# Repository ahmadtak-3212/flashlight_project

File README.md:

# Flashlight: high-power LED driver

A handheld flashlight built around a **Cree XHP50.3 (6 V)** LED. The repo holds two threads of work:

1. **The power converter** (finished, documented in the final report): a discrete, analog, constant-current **boost converter** that takes 3 V from two alkaline cells up to about 6–6.5 V and regulates the LED at about 1–1.5 A. It uses op-amps, a comparator and a gate driver, with no microcontroller in the loop. It was built as the final project for MIT 6.2222 (fall 2025), including the graduate extension.
2. **The product boards** (in progress): an STM32 controller with shake-to-wake, a USB-PD charger and power-path board, and an integrated v1.1 board meant to put everything on a single 21700-cell PCB.

📄 **Read the final report:** [`docs/reports/final_report/final_report.pdf`](docs/reports/final_report/final_report.pdf) (the Typst source is next to it). The original proposal is in [`docs/reports/proposal/`](docs/reports/proposal).

---

## Contents

- [Status](#status)
- [Repository layout](#repository-layout)
- [How the converter works](#how-the-converter-works)
- [Boards](#boards)
- [Firmware](#firmware)
- [Analysis](#analysis)
- [Mechanical](#mechanical)
- [Reproducing the design](#reproducing-the-design)
- [Results](#results)
- [Known issues and next steps](#known-issues-and-next-steps)

## Status

| Area | Status |
|---|---|
| Boost LED driver (report design) | ✅ Built and measured on the bench (1 A LED current, stable closed loop) |
| Dev boards (`boost-dev`, `boost-dev-2`, `stm32-dev`, `led`) | ✅ Routed, with JLCPCB fab and assembly files |
| USB-PD power-input board | 🟡 Routed (4 layers, KiCad 8/9, May 2026); fab outputs need regenerating (see [known issues](#known-issues-and-next-steps)) |
| Integrated board `flashlight-full-v1-1` | 🟡 Schematic only (14 sheets), not laid out |
| Firmware (STM32 shake-to-wake) | 🟡 Proof of concept (~100 lines) |
| Mechanical (body, head, optic) | 🟡 SolidWorks assembly, not yet built |

## Repository layout

```
flashlight_project/
├── docs/
│   └── reports/
│       ├── final_report/     Typst source + PDF + figures (6.2222 final report)
│       └── proposal/         project proposal (Typst + PDF)
├── electrical/               one KiCad project per board (see "Boards")
├── firmware/
│   └── flashlight-firmware-stm32/   PlatformIO project (STM32L151, Arduino core)
├── analysis/
│   └── sim/boost_transfer.m  MATLAB state-space model of the boost + PI loop
└── mechanical/
    └── cad/flashlight-v1.SLDASM     SolidWorks assembly (body, head, optic, cell)
```

See [docs/STRUCTURE.md](docs/STRUCTURE.md) for the folder conventions shared across my projects.

## How the converter works

**Power stage.** A non-synchronous boost converter: a 22 µH inductor, a low-side switch, a Schottky rectifier and a 120 µF output capacitor. The LED returns to ground through a 0.2 Ω shunt.

| Parameter | Value |
|---|---|
| Input | 3 V (2 × alkaline cells) |
| Output | ≈ 6–6.5 V at the LED, 1–1.5 A (2 A hard ceiling) |
| Switching frequency | ≈ 100 kHz |
| Duty cycle | D ≈ 0.52 |
| Average inductor current | ≈ 3.9 A (ripple ≈ 0.7 A) |
| Inductor sizing | L_min ≈ 18 µH at 20 % ripple, so 22 µH chosen |
| Shunt dissipation | 0.45–0.8 W at 1.5–2 A |

**Control loop.** This is voltage-mode PWM with an outer LED-current loop, all built from analog parts:

1. An **LM358** amplifies the shunt voltage (current sense).
2. A second **LM358** stage acts as a PI controller and outputs V_ctrl. The model maps it with R_in = 10 kΩ and R_f = 680 Ω.
3. A third **LM358** generates a 0–1 V, ~100 kHz triangle.
4. An **LM311** comparator compares V_ctrl with the triangle to produce PWM.
5. An **IR2125** high-current gate driver drives the switch; a 12 V gate supply is needed for the GaN part.

**Switch comparison.** The same power stage was run with a silicon MOSFET (**RFD3055LESM**, ~107 mΩ) and a GaN FET (**GAN041-650WSBQ**, ~41 mΩ). Estimated device loss at the operating point is ≈ 84 mW for Si versus ≈ 18 mW for GaN, and the GaN part ran visibly cooler.

**Graduate extension.** The report adds a switched-capacitor quadrupler that charges a storage capacitor for a "flash" pulse through a 1 Ω series resistor (see “Graduate Extension” in the report).

The report also covers loop-shaping with Black's feedback formula and the boost converter's right-half-plane zero. It compares voltage-mode and current-mode control, drawing on the TI application notes it cites.

## Boards

All boards are KiCad projects under `electrical/`. Board renders are generated from the committed Gerbers.

| Board | What it is | Key parts | PCB |
|---|---|---|---|
| [`flashlight-boost-dev`](electrical/flashlight-boost-dev) | First IC-based LED boost test board | TPS61169 boost LED driver, NSR0240 Schottky, 4.7 µH WE-MAPI | 2 layers, 32 × 32 mm, JLCPCB files |
| [`flashlight-boost-dev-2`](electrical/flashlight-boost-dev-2) | Higher-power IC boost test board | TPS61500, 10 µH CDRH105R, SS36 3 A Schottky | 2 layers, 33 × 33 mm, JLCPCB files |
| [`flashlight-stm32-dev`](electrical/flashlight-stm32-dev) | "STM32L151C8 Battery Dev Board": controller and charging bring-up | STM32L151C8, BQ25185 charger/power path, MMA8452Q accelerometer, 2 × MCP1703A LDO, USB-C, ST-LINK header, 2 × 12 GPIO headers, RGB LED, 8 MHz + 32.768 kHz crystals | 6 layers, 120 × 35 mm, 99 parts, JLCPCB files |
| [`flashlight-led`](electrical/flashlight-led) | Small round LED carrier board | 3 LEDs, +18 V input | 2 layers, JLCPCB files |
| [`flashlight-power-input-dev`](electrical/flashlight-power-input-dev) | "100 W Power Delivery + Charger Module" | CYPD3177 USB-PD sink, BQ25792 buck-boost charger, BQ297xx protector, 4 × CSD16406Q3, 2 × LM5050-1 ideal diodes, TPS61222, TLV733, 21700 cell | 4 layers, 100 × 30 mm, 97 parts |
| [`flashlight-full-v1-1`](electrical/flashlight-full-v1-1) | Integrated flashlight (schematic) | STM32F070F6P, TPS61088 boost, BQ25185, BQ27220 fuel gauge, MMA8452Q, TMP102, INA180A1, MCP4017 digipot, IR2125, LM358 × 3, LM311, 74HC14, 2 × XHP50.3, 21700 cell, USB-C | 6-layer stackup, 14 schematic sheets, not laid out |
| `flashlight-hardware` | Empty placeholder project | — | — |

The early plan used TI boost-LED ICs (the two `boost-dev` boards). They could not deliver the current the XHP50.3 needs, which is why the report design went discrete.

<details>
<summary>Board renders (top and bottom)</summary>

**flashlight-boost-dev** (TPS61169)

**flashlight-boost-dev-2** (TPS61500)

**flashlight-stm32-dev**

</details>

## Firmware

`firmware/flashlight-firmware-stm32` is a PlatformIO project for the STM32L151 dev board. It shows the shake-to-toggle behavior:

- It configures the MMA8452Q **transient (shake) detector** over I²C on PB7/PB6: X/Y axes, threshold 12 (≈ 0.75 g), 25 × 20 ms debounce.
- The accelerometer interrupt on **PA0** wakes the MCU from deep sleep through `STM32LowPower`, and each shake toggles the output on **PB9**.

| Setting | Value |
|---|---|
| Platform | `ststm32`, Arduino framework |
| Board definition | `rak811_tracker` (an STM32L151 board used as a stand-in), with a local `boards/` directory |
| Libraries | `sparkfun/SparkFun_MMA8452Q ^1.4.0`, `stm32duino/STM32duino Low Power ^1.4.0` |
| Upload | `serial`: the STM32 ROM UART bootloader (hold BOOT0 high and reset) |

```bash
cd firmware/flashlight-firmware-stm32
pio run                     # build
pio run -t upload           # flash over the UART bootloader
# or use the board's ST-LINK header: set upload_protocol = stlink in platformio.ini
```

## Analysis

`analysis/sim/boost_transfer.m` (MATLAB) builds the averaged small-signal model of the boost, including the RHP zero. It wraps the PI controller around that model as an augmented state-space system, then plots the loop Bode response and the closed-loop setpoint step. Run it in MATLAB with the Control System Toolbox. The listing is also in the report appendix.

| Loop gain | Step response |
|---|---|
|  |  |

## Mechanical

`mechanical/cad/flashlight-v1.SLDASM` (SolidWorks) contains the body, head, a TIR 60° optic, an 18650 cell model, a copper slug for the LED, and the LED PCB. Mounting holders for the dev boards are in `electrical/<board>/holder/` (SLDPRT and STEP).

## Reproducing the design

| What | Tool |
|---|---|
| Schematics and PCBs | KiCad 8 or newer. `flashlight-power-input-dev` was last saved in KiCad 9. Projects use `${KIPRJMOD}`-relative libraries in each board's `libs/` folder. |
| PCB fab and assembly | Each board has `jlcpcb/gerber/` and `jlcpcb/production_files/` (Gerber zip, BOM and CPL) for JLCPCB. |
| Report | [Typst](https://typst.app) (`typst compile final_report.typ`) |
| Model | MATLAB with the Control System Toolbox |
| Firmware | PlatformIO (VS Code extension or `pio` CLI) |
| CAD | SolidWorks |

**Rebuilding the report converter on a bench.** Component values and schematic blocks are in the report's “Circuit Design and Analysis” chapter, which covers the power stage, current sense and PI loop, magnetics, and switch choice. “Hardware Implementation and Measurement Setup” covers the bench setup.

Bring-up order, from the report:
1. Run the boost open-loop at a fixed duty cycle into a resistive load.
2. Close the current loop at a low setpoint.
3. Raise the setpoint to the LED operating point.

The two fixes that mattered were:
- an RC filter (100 Ω / 1 nF) on the current-sense signal, and
- hysteresis on the LM311 comparator to stop chatter.

## Results

- The loop is closed and stable at about **1 A LED current** from a 3 V input. The output is 6–6.5 V, and the measured duty cycle is ≈ 0.5, close to the 0.52 predicted.
- The setpoint step response is well damped, as the MATLAB model predicts. Remaining differences come from LM358 bandwidth, comparator delay and the non-ideal ramp.
- GaN vs Si: both reach the same operating point, and the GaN FET runs cooler.
- The LED case settles near **70 °C** at the operating point. That is acceptable, but heatsinking through the copper slug is required.

| Bench setup | Thermal |
|---|---|
|  |  |

## Known issues and next steps

- The Gerbers in `electrical/flashlight-power-input-dev/jlcpcb/` are **copies of the mp3 player board**, left over from the project template. Regenerate them from `flashlight-power-input-dev.kicad_pcb` before ordering.
- `flashlight-full-v1-1` still needs layout. It merges the report's analog current loop (LM358/LM311/IR2125) with the STM32 controller, charger and fuel gauge.
- Firmware still needs brightness control through the digipot or PWM setpoint, battery reporting from the BQ27220, and thermal limiting from the TMP102.

## Author

Ahmad Taka.

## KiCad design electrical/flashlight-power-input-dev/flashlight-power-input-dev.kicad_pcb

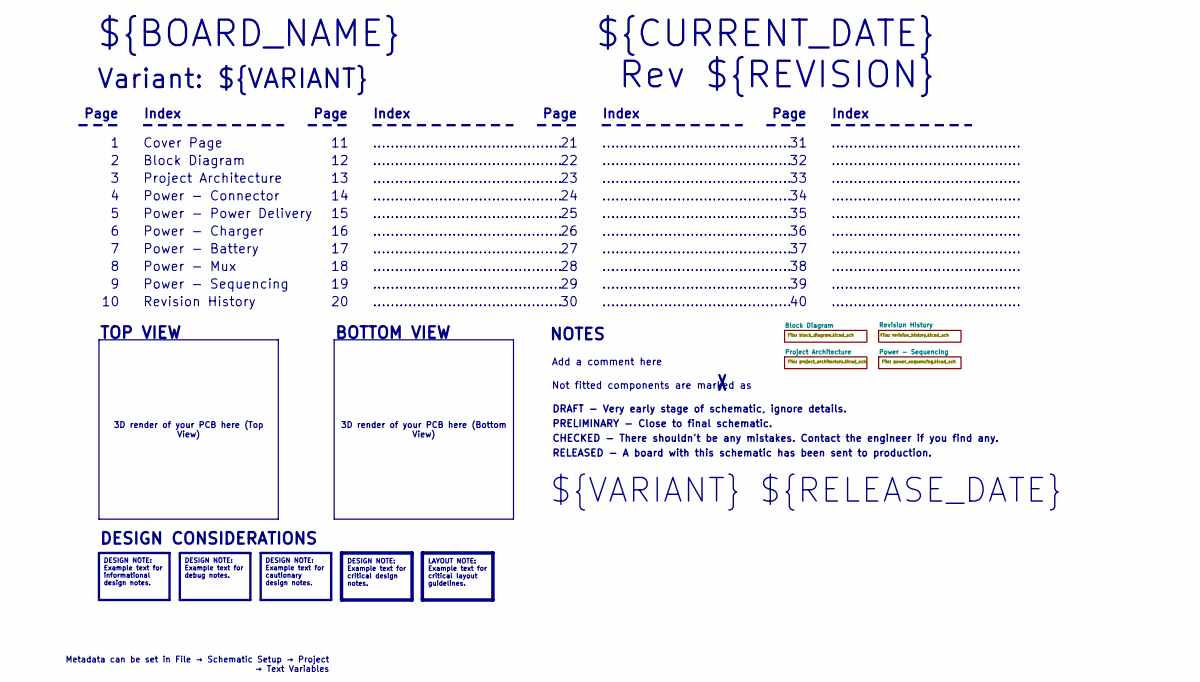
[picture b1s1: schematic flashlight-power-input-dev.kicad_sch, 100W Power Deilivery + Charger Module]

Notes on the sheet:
BOTTOM VIEW
...........................................
RELEASED - A board with this schematic has been sent to production.
Page
TOP VIEW
Revision History
Power - Sequencing
Power - Mux
Not fitted components are marked as
Index
PRELIMINARY - Close to final schematic.
${VARIANT} ${RELEASE_DATE}
Power - Connector
${CURRENT_DATE}
Variant: ${VARIANT}
Rev ${REVISION}
Power - Power Delivery
${BOARD_NAME}
DRAFT - Very early stage of schematic, ignore details.
Power - Charger
Block Diagram
Add a comment here
Cover Page
NOTES
Project Architecture
CHECKED - There shouldn't be any mistakes. Contact the engineer if you find any.
DESIGN CONSIDERATIONS
Power - Battery
3D render of your PCB here (Bottom View)
3D render of your PCB here (Top View)
Metadata can be set in File → Schematic Setup → Project → Text Variables
DESIGN NOTE: Example text for informational design notes.
LAYOUT NOTE: Example text for critical layout guidelines.
DESIGN NOTE: Example text for cautionary design notes.
DESIGN NOTE: Example text for debug notes.
DESIGN NOTE: Example text for critical design notes.

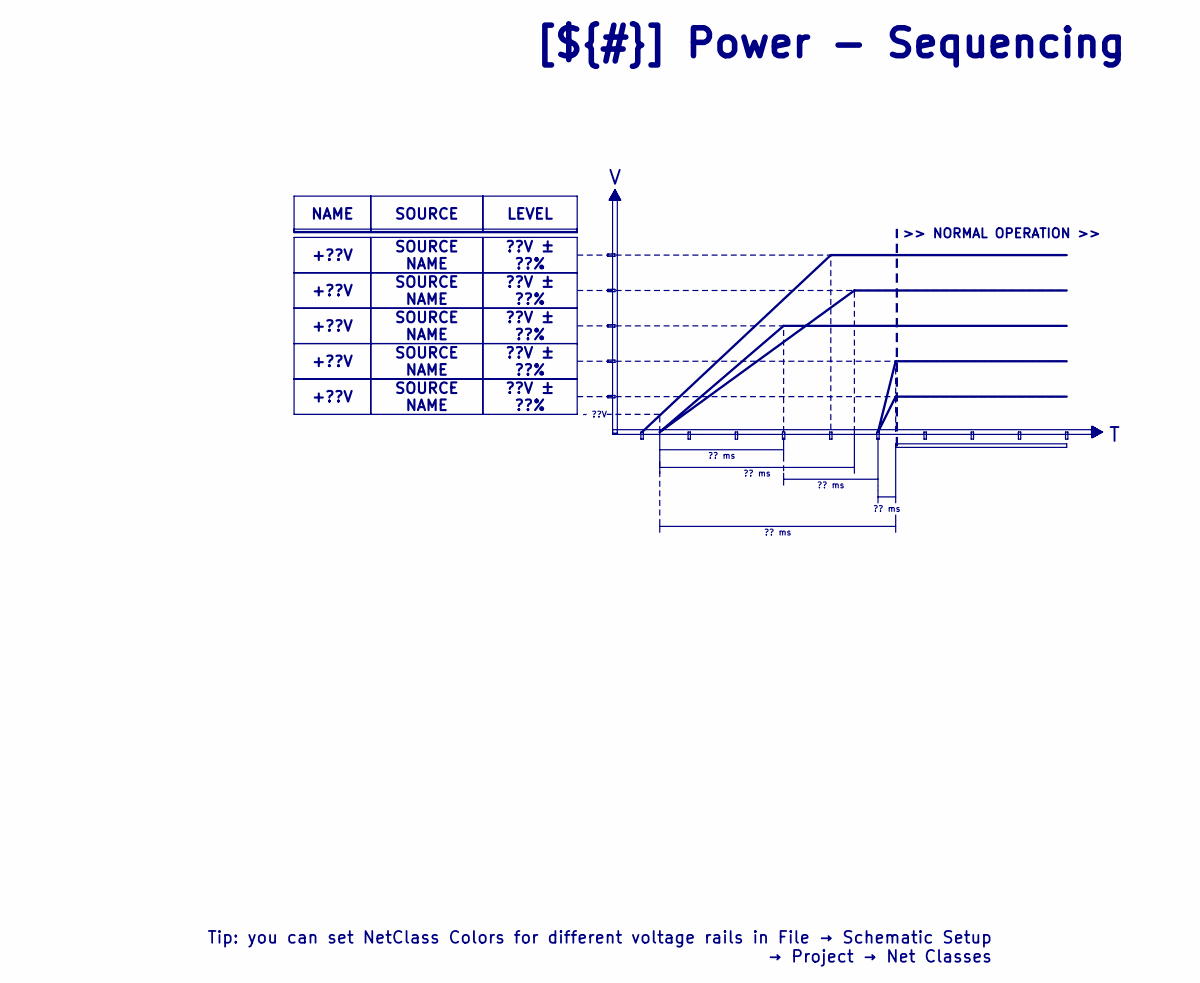
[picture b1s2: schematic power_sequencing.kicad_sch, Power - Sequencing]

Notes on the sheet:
>> NORMAL OPERATION >>
LEVEL
+??V
SOURCE NAME
?? ms
??V ± ??%
[${#}] ${TITLE}
~ ??V
NAME
SOURCE
Tip: you can set NetClass Colors for different voltage rails in File → Schematic Setup → Project → Net Classes

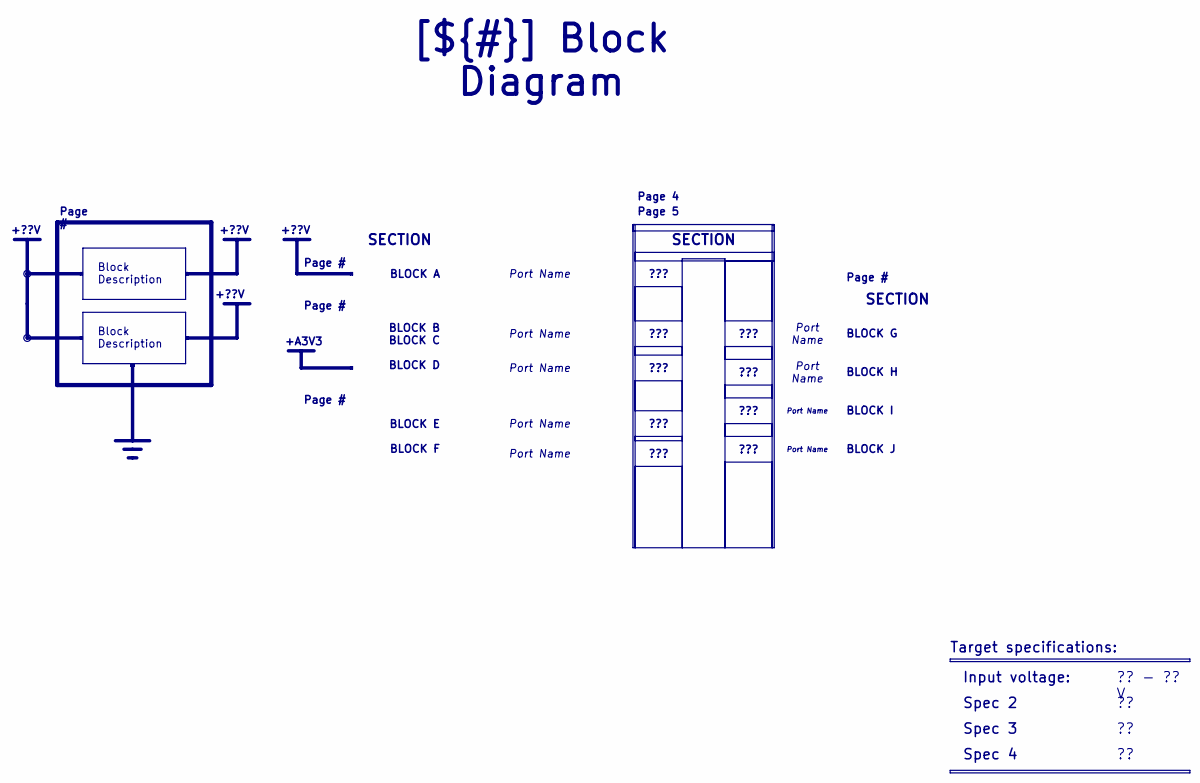
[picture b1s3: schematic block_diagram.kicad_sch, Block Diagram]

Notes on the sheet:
+??V
+A3V3
Spec 3
Block Description
???
Spec 2
Port Name
SECTION
Page #
Input voltage:
BLOCK E BLOCK F
BLOCK A
BLOCK I
BLOCK G
[${#}] ${TITLE}
Target specifications:
?? - ?? V
Page 4
BLOCK J
Page 5
BLOCK B BLOCK C BLOCK D
Spec 4
BLOCK H

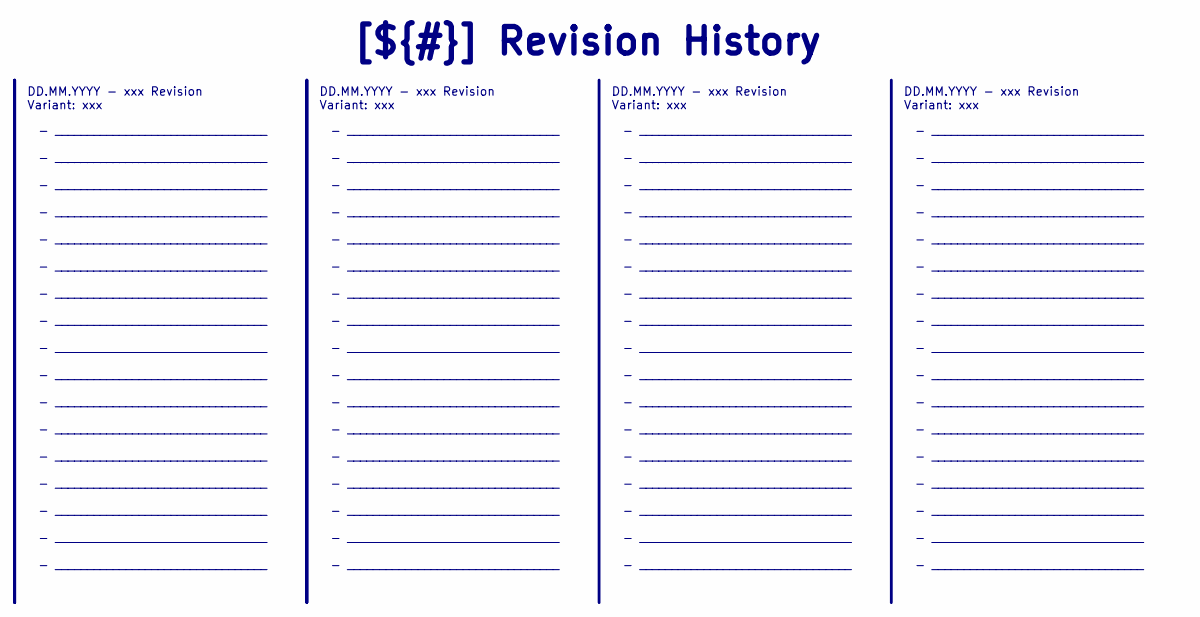
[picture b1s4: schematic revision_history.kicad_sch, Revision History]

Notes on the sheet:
- _________________________________ - _________________________________ - _________________________________ - _________________________________ - _________________________________ - _________________________________ - _________________________________ - _________________________________ - _________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
DD.MM.YYYY - xxx Revision Variant: xxx
[${#}] ${TITLE}

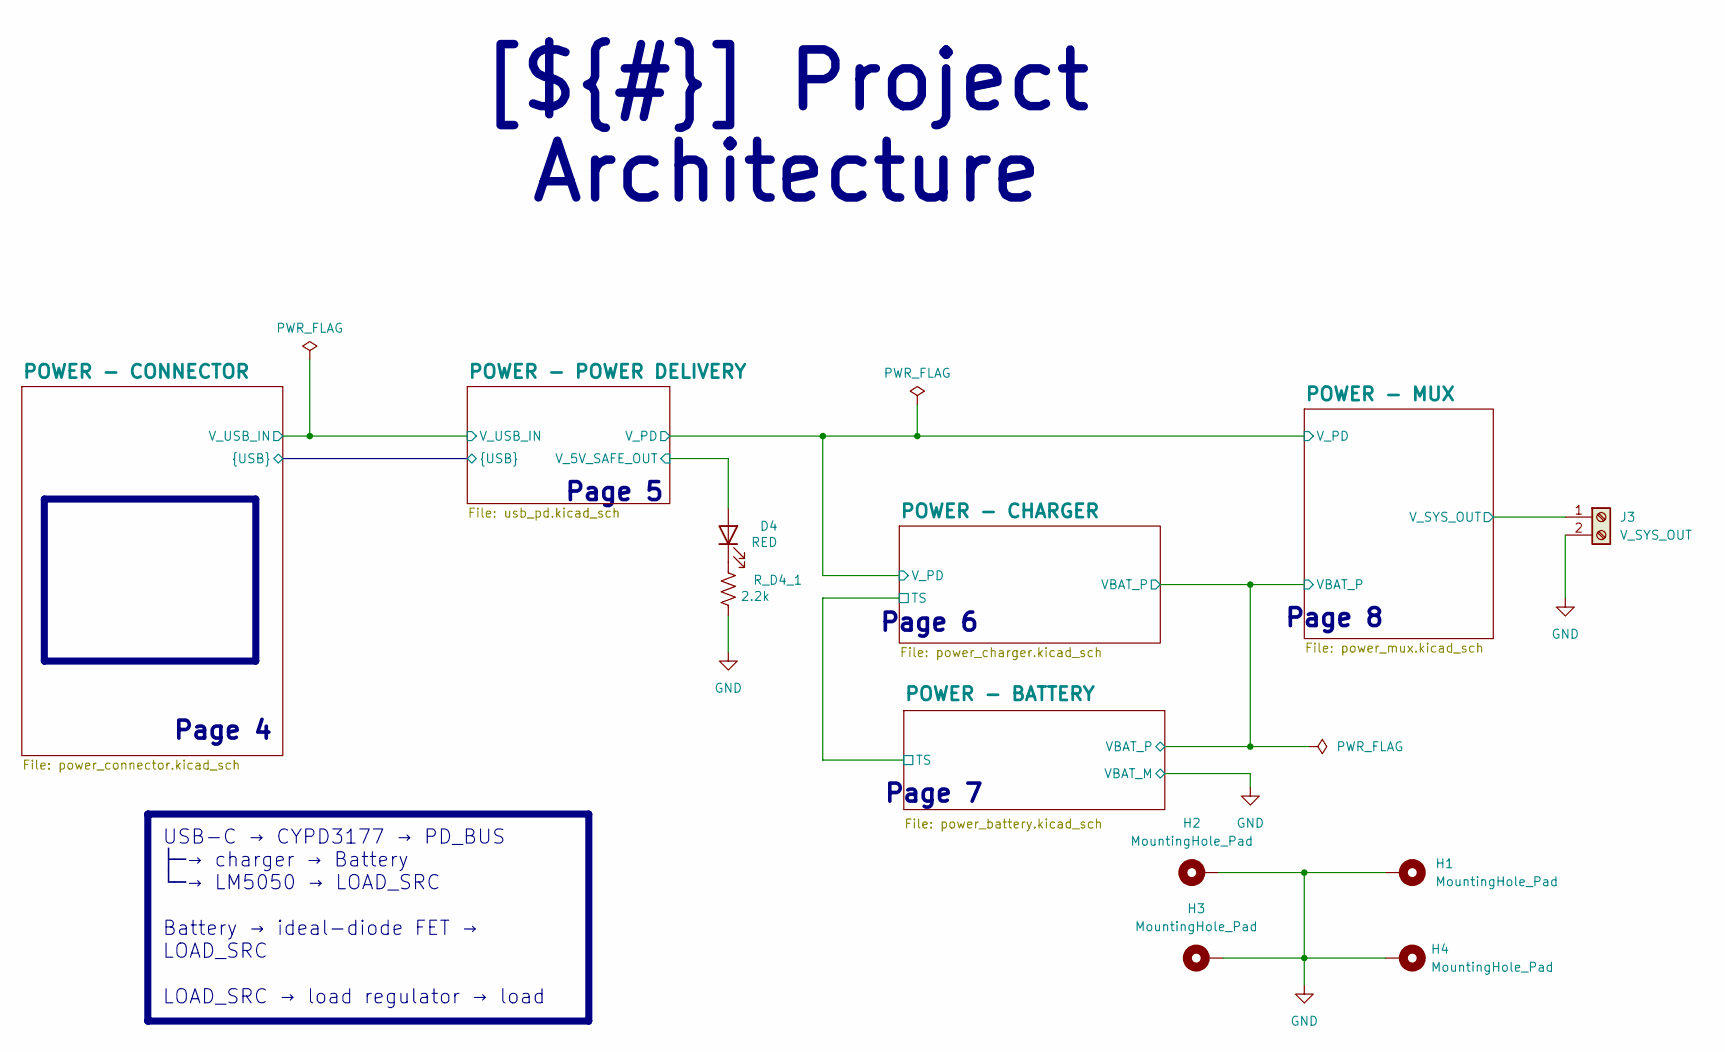
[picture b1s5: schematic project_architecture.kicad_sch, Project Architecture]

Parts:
D4: RED; LED_0603_1608Metric; LCSC C2286
H1, H2, H3, H4: MountingHole_Pad; MountingHole_3.2mm_M3_DIN965_Pad
J3: V_SYS_OUT; TerminalBlock_Phoenix_MKDS-1,5-2-5.08_1x02_P5.08mm_Horizont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
R_D4_1: 2.2k; R_0402_1005Metric; LCSC C25091

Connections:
/Project Architecture/POWER - MUX/V_SYS_OUT: J3.1; also elsewhere on the board
/Project Architecture/POWER - POWER DELIVERY/V_5V_SAFE_OUT: D4.2 (A); also elsewhere on the board
GND: H1.1 (1_1), H2.1 (1_1), H3.1 (1_1), H4.1 (1_1), J3.2, R_D4_1.1; also elsewhere on the board
unnamed: D4.1 (K), R_D4_1.2

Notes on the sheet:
Page 8
Page 5
Page 4
Page 6
Page 7
USB-C → CYPD3177 → PD_BUS ├─→ charger → Battery └─→ LM5050 → LOAD_SRC Battery → ideal-diode FET → LOAD_SRC LOAD_SRC → load regulator → load
[${#}] ${TITLE}

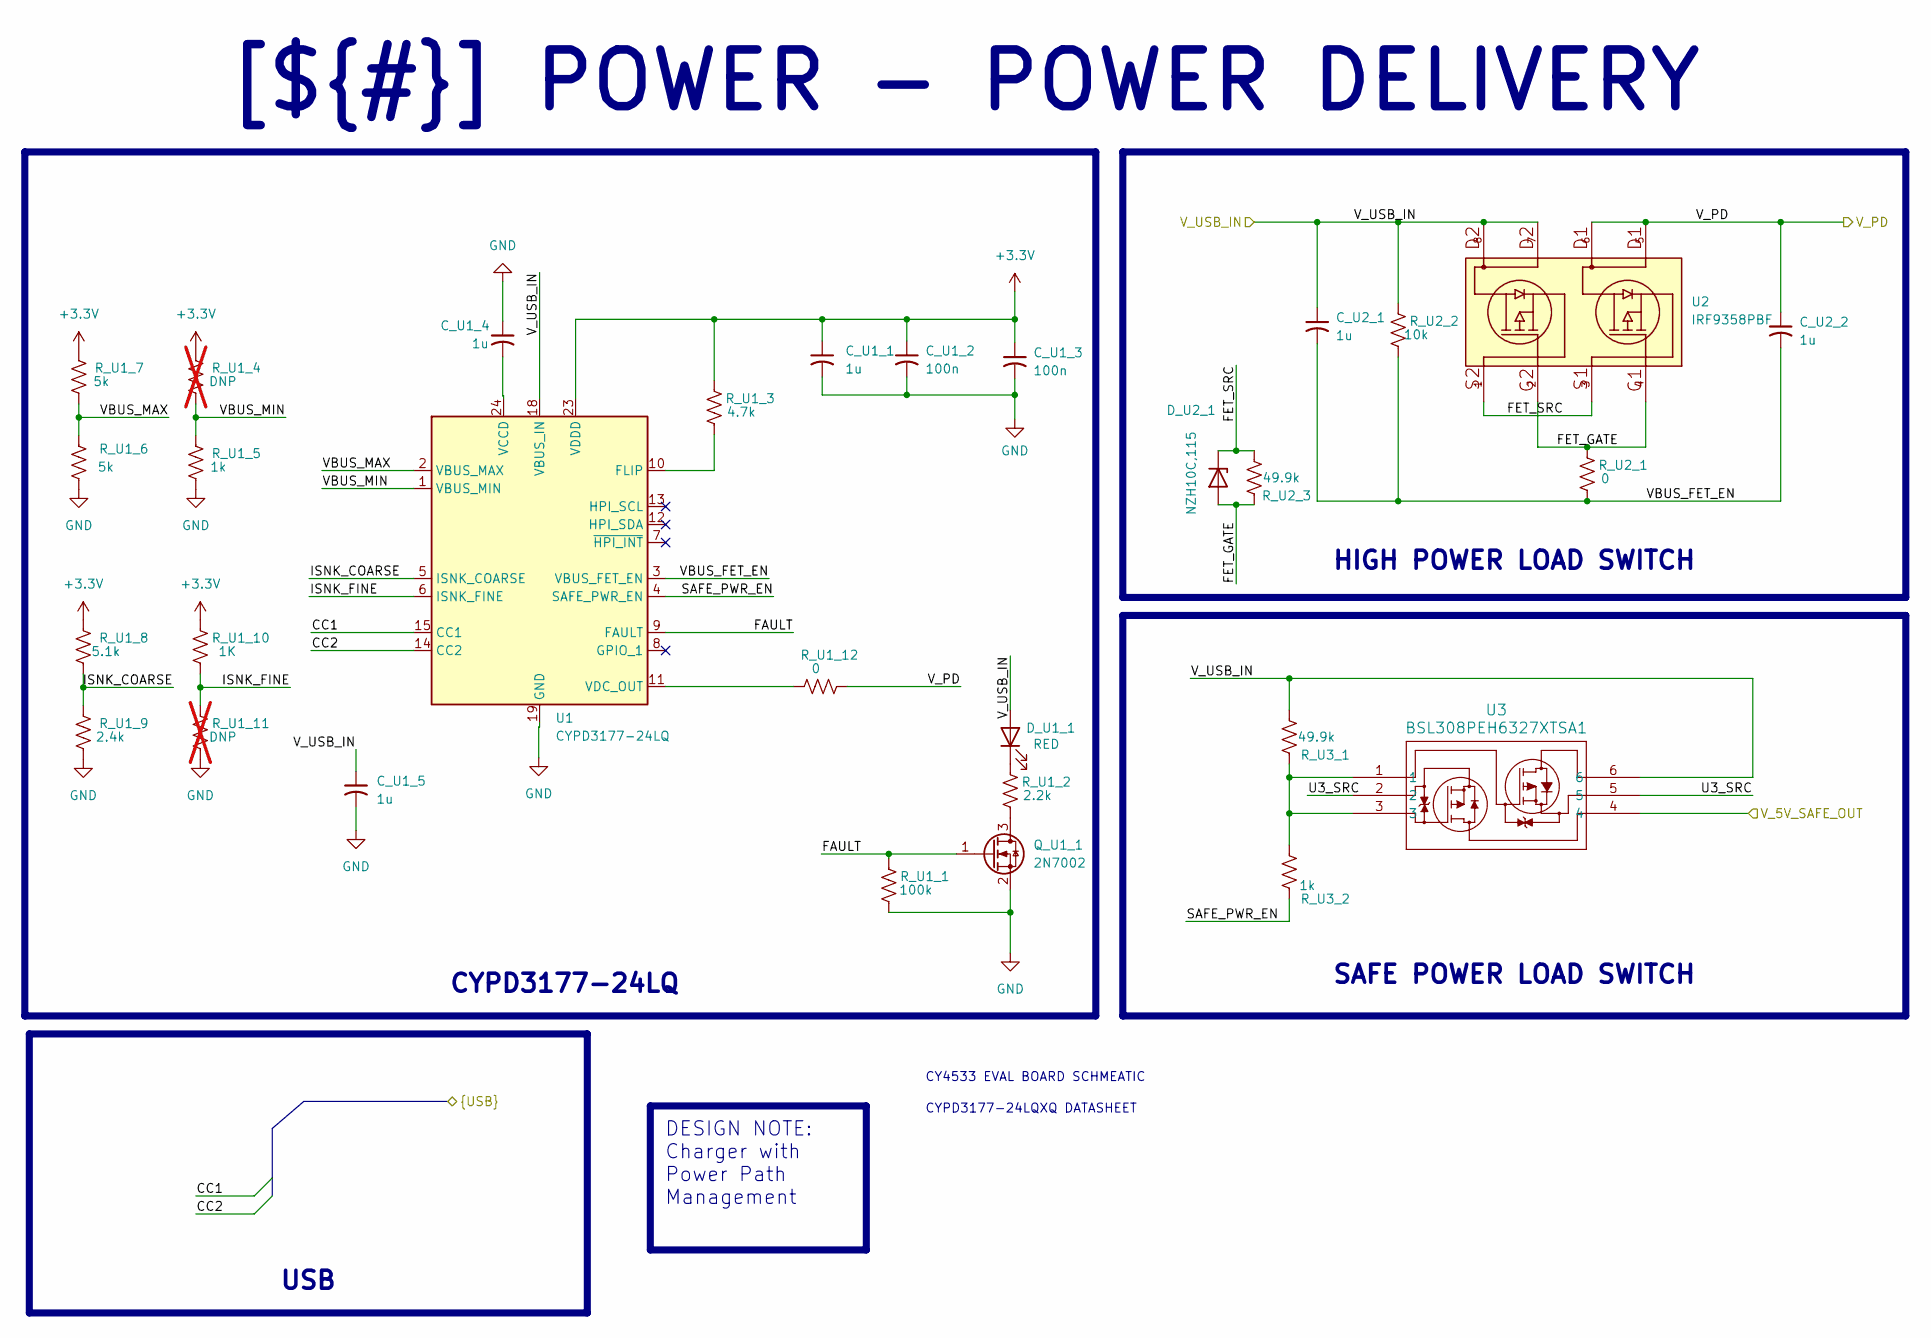
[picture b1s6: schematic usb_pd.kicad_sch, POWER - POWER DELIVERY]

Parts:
C_U1_1, C_U1_5, C_U2_1, C_U2_2: 1u; R_0603_1608Metric_Pad0.98x0.95mm_HandSolder
C_U1_2, C_U1_3: 100n; C_0402_1005Metric
C_U1_4: 1u; C_0402_1005Metric
D_U1_1: RED; LED_0603_1608Metric; LCSC C2286
D_U2_1: NZH10C,115; D_SOD-123F
Q_U1_1: 2N7002; SOT-23
R_U1_1: 100k; R_0402_1005Metric; LCSC C25091
R_U1_2: 2.2k; R_0402_1005Metric; LCSC C25091
R_U1_3: 4.7k; R_0402_1005Metric; LCSC C25091
R_U1_4, R_U1_11: DNP; R_0603_1608Metric_Pad0.98x0.95mm_HandSolder; LCSC C25091; not fitted
R_U1_5, R_U3_2: 1k; R_0603_1608Metric_Pad0.98x0.95mm_HandSolder; LCSC C25091
R_U1_6, R_U1_7: 5k; R_0603_1608Metric_Pad0.98x0.95mm_HandSolder; LCSC C25091
R_U1_8: 5.1k; R_0603_1608Metric_Pad0.98x0.95mm_HandSolder; LCSC C25091
R_U1_9: 2.4k; R_0603_1608Metric_Pad0.98x0.95mm_HandSolder; LCSC C25091
R_U1_10: 1K; R_0603_1608Metric_Pad0.98x0.95mm_HandSolder; LCSC C25091
R_U1_12, R_U2_1: 0; R_0603_1608Metric_Pad0.98x0.95mm_HandSolder; LCSC C25091
R_U2_2: 10k; R_0603_1608Metric_Pad0.98x0.95mm_HandSolder; LCSC C25091
R_U2_3, R_U3_1: 49.9k; R_0603_1608Metric_Pad0.98x0.95mm_HandSolder; LCSC C25091
U1: CYPD3177-24LQ; QFN-24-1EP_4x4mm_P0.5mm_EP2.75x2.75mm
U2: IRF9358PBF; SOIC8-150
U3: BSL308PEH6327XTSA1; PG-TSOP6-6-4_INF

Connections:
+3.3V: C_U1_1.1, C_U1_2.1, C_U1_3.1, R_U1_3.2, R_U1_4.2, R_U1_7.2, R_U1_8.2, R_U1_10.2, U1.23 (VDDD)
/Project Architecture/POWER - CHARGER/V_PD: C_U2_2.1, R_U1_12.1, U2.5, U2.6; also elsewhere on the board
/Project Architecture/POWER - CONNECTOR/CC1: U1.15 (CC1); also elsewhere on the board
/Project Architecture/POWER - CONNECTOR/CC2: U1.14 (CC2); also elsewhere on the board
/Project Architecture/POWER - POWER DELIVERY/FAULT: Q_U1_1.1 (G), R_U1_1.2, U1.9 (FAULT)
/Project Architecture/POWER - POWER DELIVERY/FET_GATE: D_U2_1.2 (A), R_U2_1.2, R_U2_3.1, U2.2, U2.4
/Project Architecture/POWER - POWER DELIVERY/FET_SRC: D_U2_1.1 (K), R_U2_3.2, U2.1, U2.3
/Project Architecture/POWER - POWER DELIVERY/ISNK_COARSE: R_U1_8.1, R_U1_9.2, U1.5 (ISNK_COARSE)
/Project Architecture/POWER - POWER DELIVERY/ISNK_FINE: R_U1_10.1, R_U1_11.2, U1.6 (ISNK_FINE)
/Project Architecture/POWER - POWER DELIVERY/SAFE_PWR_EN: R_U3_2.1, U1.4 (SAFE_PWR_EN)
/Project Architecture/POWER - POWER DELIVERY/U3_SRC: U3.2, U3.5
/Project Architecture/POWER - POWER DELIVERY/VBUS_FET_EN: C_U2_1.2, C_U2_2.2, R_U2_1.1, R_U2_2.1, U1.3 (VBUS_FET_EN)
/Project Architecture/POWER - POWER DELIVERY/VBUS_MAX: R_U1_6.2, R_U1_7.1, U1.2 (VBUS_MAX)
/Project Architecture/POWER - POWER DELIVERY/VBUS_MIN: R_U1_4.1, R_U1_5.2, U1.1 (VBUS_MIN)
/Project Architecture/POWER - POWER DELIVERY/V_5V_SAFE_OUT: U3.4; also elsewhere on the board
/Project Architecture/POWER - POWER DELIVERY/V_USB_IN: C_U1_5.1, C_U2_1.1, D_U1_1.2 (A), R_U2_2.2, R_U3_1.2, U1.18 (VBUS_IN), U2.7, U2.8, U3.6; also elsewhere on the board
GND: C_U1_1.2, C_U1_2.2, C_U1_3.2, C_U1_4.1, C_U1_5.2, Q_U1_1.2 (S), R_U1_1.1, R_U1_5.1, R_U1_6.1, R_U1_9.1, R_U1_11.1, U1.19 (GND), U1.22 (GND), U1.25 (GND); also elsewhere on the board
unnamed: D_U1_1.1 (K), R_U1_2.2
unnamed: Q_U1_1.3 (D), R_U1_2.1
unnamed: R_U3_1.1, R_U3_2.2, U3.1, U3.3
unnamed: R_U1_3.1, U1.10 (FLIP)
unnamed: C_U1_4.2, U1.24 (VCCD)
unnamed: R_U1_12.2, U1.11 (VDC_OUT)

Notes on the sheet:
CYPD3177-24LQXQ DATASHEET
CY4533 EVAL BOARD SCHMEATIC
[${#}] ${TITLE}
CYPD3177-24LQ
SAFE POWER LOAD SWITCH
DESIGN NOTE: Charger with Power Path Management
USB
HIGH POWER LOAD SWITCH

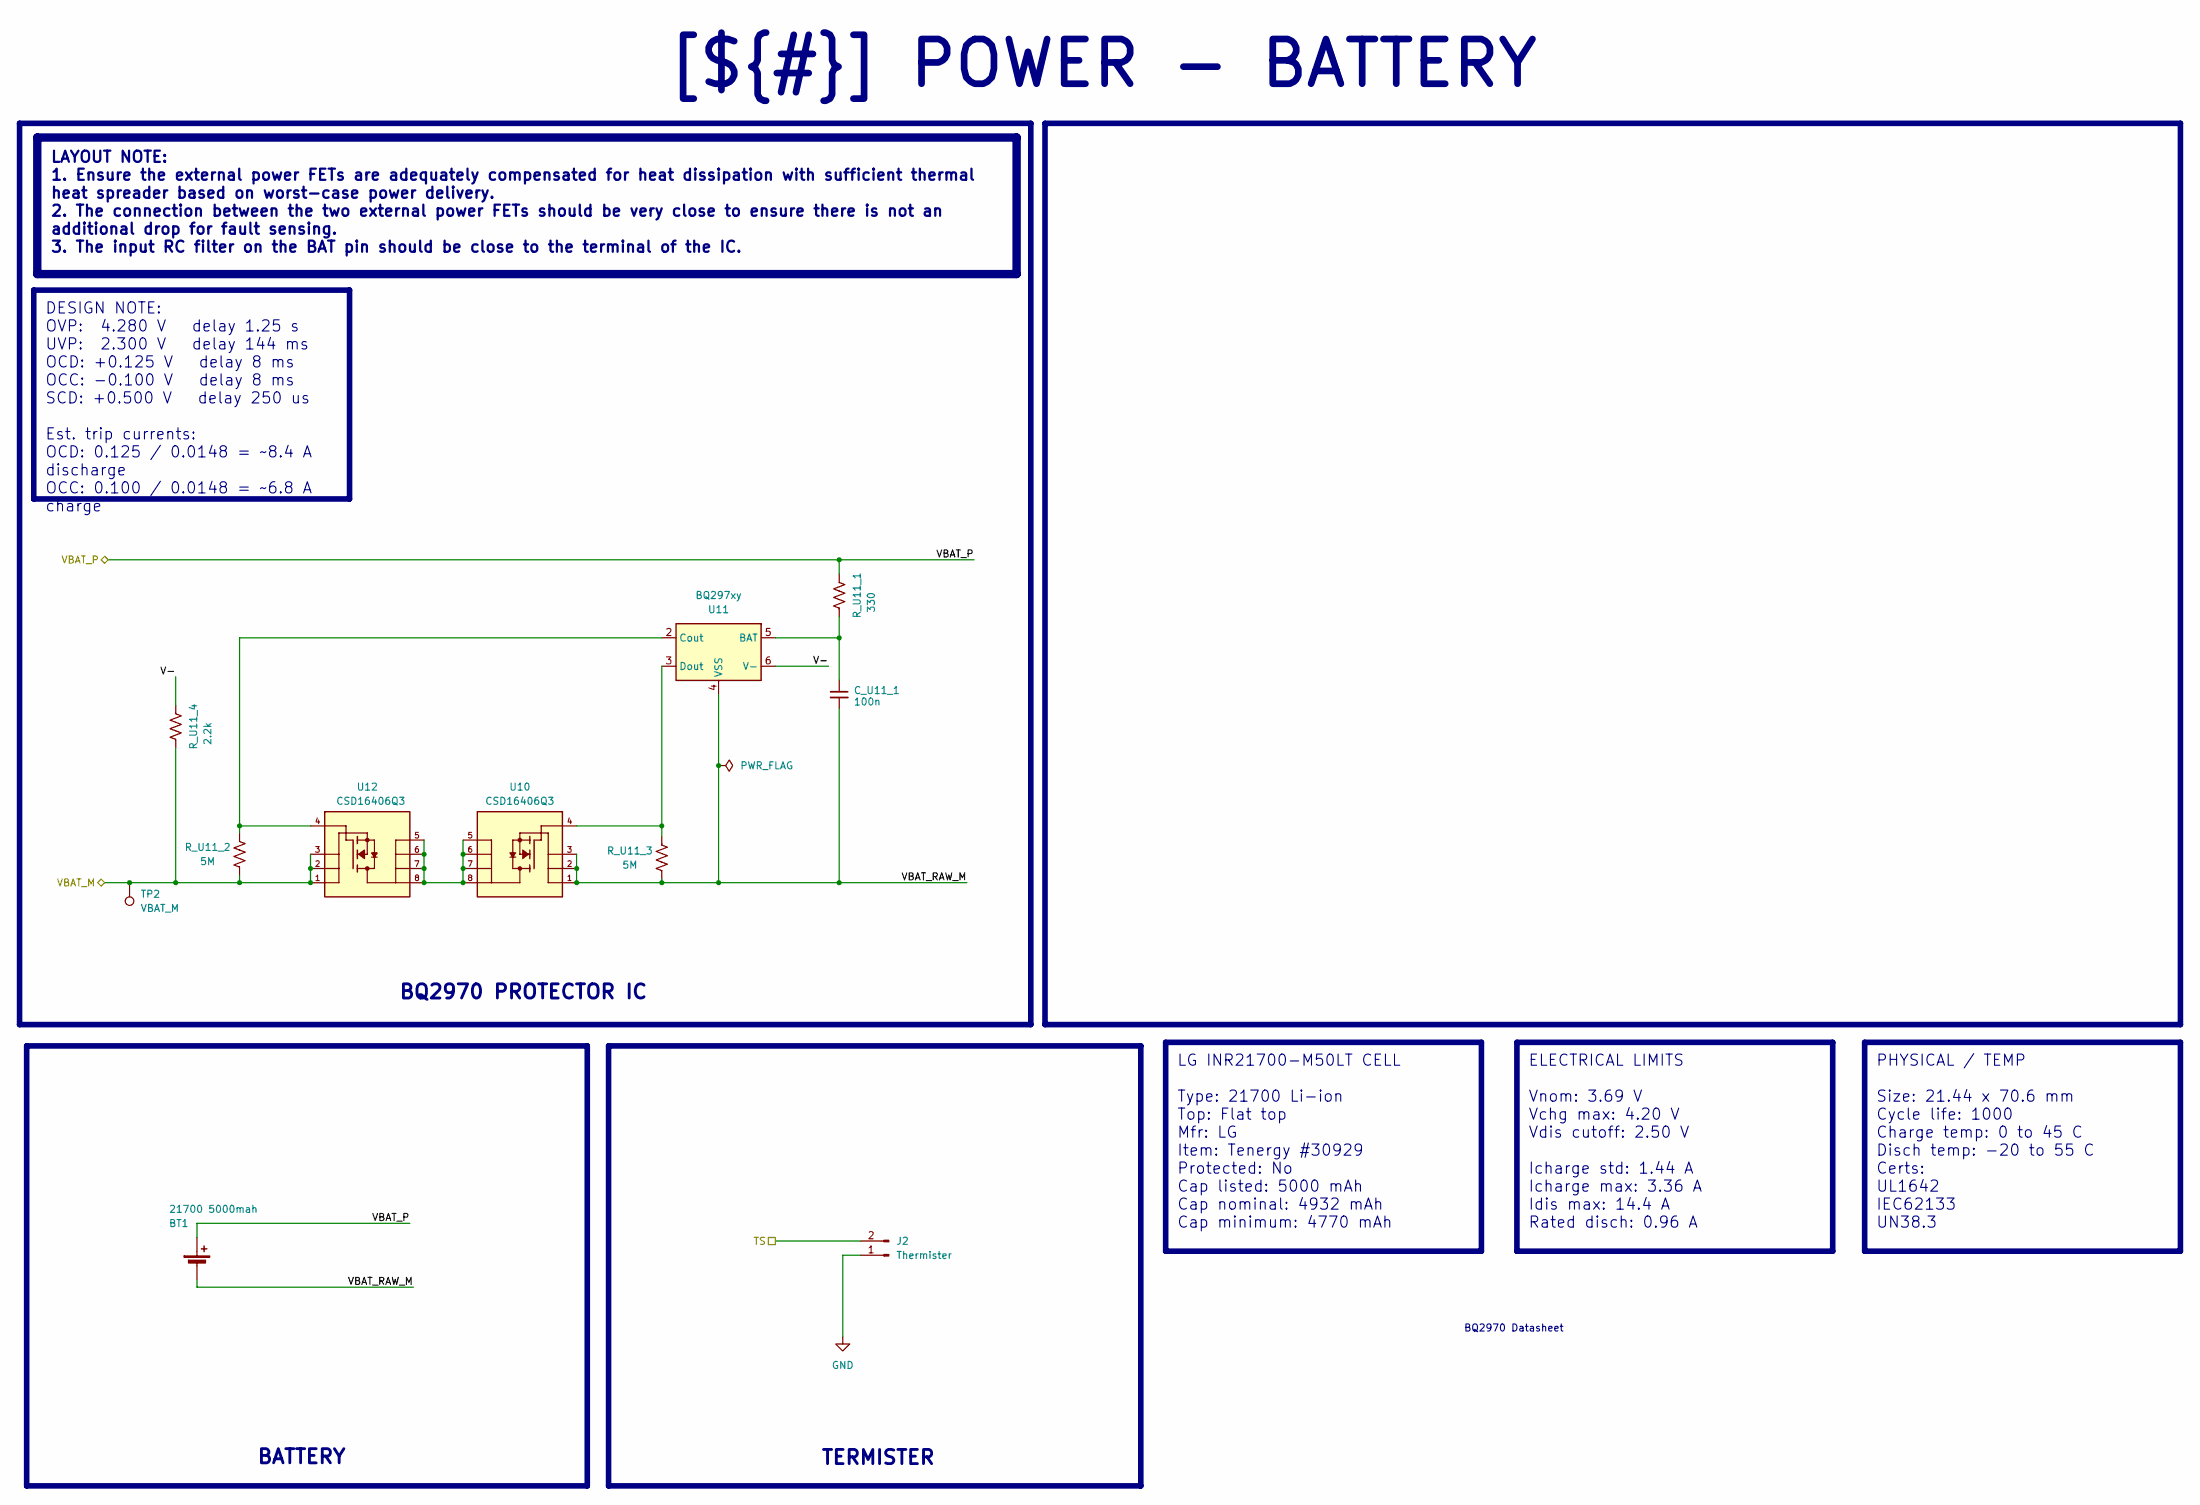
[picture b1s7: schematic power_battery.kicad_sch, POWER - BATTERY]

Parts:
BT1: 21700 5000mah; BISTOOK_BATTERY_HOLDER_21700
C_U11_1: 100n; C_0603_1608Metric; LCSC C1525
J2: Thermister; PinHeader_1x02_P2.54mm_Vertical
R_U11_1: 330; R_0603_1608Metric_Pad0.98x0.95mm_HandSolder; LCSC C25091
R_U11_2, R_U11_3: 5M; R_0603_1608Metric_Pad0.98x0.95mm_HandSolder; LCSC C25091
R_U11_4: 2.2k; R_0603_1608Metric_Pad0.98x0.95mm_HandSolder; LCSC C25091
TP2: VBAT_M; TestPoint_Pad_D1.5mm
U10, U12: CSD16406Q3; TRANS_CSD16406Q3
U11: BQ297xy; WSON-6_1.5x1.5mm_P0.5mm

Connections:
/Project Architecture/POWER - BATTERY/TS: J2.2; also elsewhere on the board
/Project Architecture/POWER - BATTERY/V-: R_U11_4.1, U11.6 (V-)
/Project Architecture/POWER - BATTERY/VBAT_P: BT1.1 (+), R_U11_1.1; also elsewhere on the board
/Project Architecture/POWER - BATTERY/VBAT_RAW_M: BT1.2 (-), C_U11_1.2, R_U11_3.1, U10.1, U10.2, U10.3, U11.4 (VSS)
GND: J2.1, R_U11_2.1, R_U11_4.2, TP2.1 (1_1), U12.1, U12.2, U12.3; also elsewhere on the board
unnamed: U10.5, U10.6, U10.7, U10.8, U12.5, U12.6, U12.7, U12.8
unnamed: C_U11_1.1, R_U11_1.2, U11.5 (BAT)
unnamed: R_U11_2.2, U11.2 (Cout), U12.4
unnamed: R_U11_3.2, U10.4, U11.3 (Dout)

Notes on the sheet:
BQ2970 Datasheet
TERMISTER
BATTERY
DESIGN NOTE: OVP: 4.280 V delay 1.25 s UVP: 2.300 V delay 144 ms OCD: +0.125 V delay 8 ms OCC: -0.100 V delay 8 ms SCD: +0.500 V delay 250 us Est. trip currents: OCD: 0.125 / 0.0148 = ~8.4 A discharge OCC: 0.100 / 0.0148 = ~6.8 A charge
PHYSICAL / TEMP Size: 21.44 x 70.6 mm Cycle life: 1000 Charge temp: 0 to 45 C Disch temp: -20 to 55 C Certs: UL1642 IEC62133 UN38.3
[${#}] ${TITLE}
LAYOUT NOTE: 1. Ensure the external power FETs are adequately compensated for heat dissipation with sufficient thermal heat spreader based on worst-case power delivery. 2. The connection between the two external power FETs should be very close to ensure there is not an additional drop for fault sen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
ELECTRICAL LIMITS Vnom: 3.69 V Vchg max: 4.20 V Vdis cutoff: 2.50 V Icharge std: 1.44 A Icharge max: 3.36 A Idis max: 14.4 A Rated disch: 0.96 A
LG INR21700-M50LT CELL Type: 21700 Li-ion Top: Flat top Mfr: LG Item: Tenergy #30929 Protected: No Cap listed: 5000 mAh Cap nominal: 4932 mAh Cap minimum: 4770 mAh
BQ2970 PROTECTOR IC

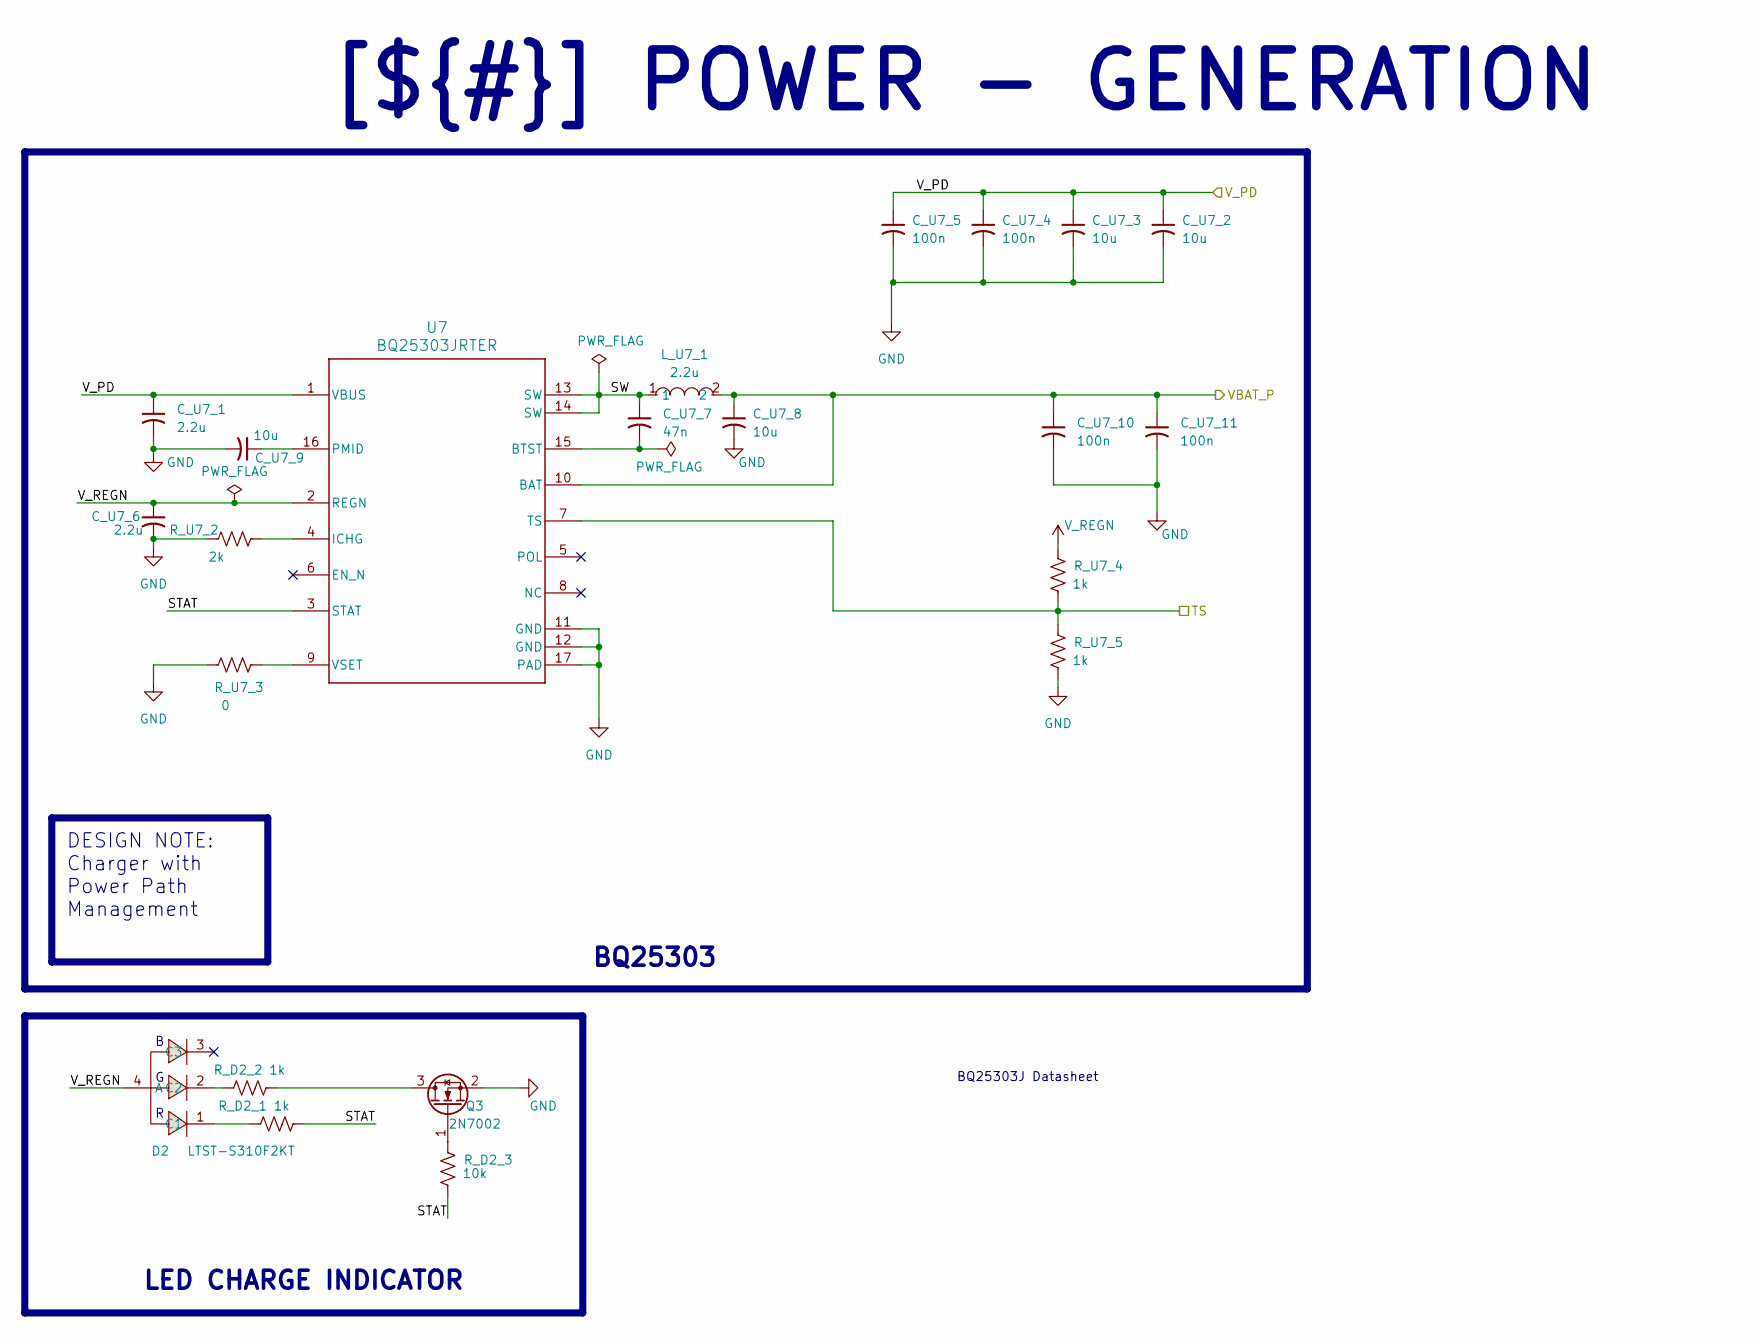
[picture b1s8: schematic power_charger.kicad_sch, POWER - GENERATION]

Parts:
C_U7_1, C_U7_6: 2.2u; C_0402_1005Metric
C_U7_2, C_U7_3, C_U7_8, C_U7_9: 10u; C_0603_1608Metric
C_U7_4, C_U7_5, C_U7_10, C_U7_11: 100n; C_0402_1005Metric
C_U7_7: 47n; C_0402_1005Metric
D2: LTST-S310F2KT; LED-SMD_4P-L3.2-W1.5_LTST-S310F2KT; LCSC Part C284950
L_U7_1: 2.2u; IND-SMD_L5.0-W5.0_SWPA5040S; MPN NR5040-2R2MTSX01; LCSC Part C22459305
Q3: 2N7002; SOT-23
R_D2_1, R_D2_2: 1k; R_0402_1005Metric; LCSC C25744
R_D2_3: 10k; R_0402_1005Metric; LCSC C25091
R_U7_2: 2k; R_0402_1005Metric; LCSC C25091
R_U7_3: 0; R_0402_1005Metric; LCSC C25091
R_U7_4, R_U7_5: 1k; R_0402_1005Metric; LCSC C25091
U7: BQ25303JRTER; RTE0016C_NV

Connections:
/Project Architecture/POWER - BATTERY/TS: R_U7_4.2, R_U7_5.1, U7.7 (TS); also elsewhere on the board
/Project Architecture/POWER - BATTERY/VBAT_P: C_U7_8.1, C_U7_10.1, C_U7_11.1, L_U7_1.2, U7.10 (BAT); also elsewhere on the board
/Project Architecture/POWER - CHARGER/STAT: R_D2_1.1, R_D2_3.1, U7.3 (STAT)
/Project Architecture/POWER - CHARGER/SW: C_U7_7.1, L_U7_1.1, U7.13 (SW), U7.14 (SW)
/Project Architecture/POWER - CHARGER/V_PD: C_U7_1.1, C_U7_2.1, C_U7_3.1, C_U7_4.1, C_U7_5.1, U7.1 (VBUS); also elsewhere on the board
GND: C_U7_1.2, C_U7_2.2, C_U7_3.2, C_U7_4.2, C_U7_5.2, C_U7_6.2, C_U7_8.2, C_U7_9.2, C_U7_10.2, C_U7_11.2, Q3.2 (S), R_U7_2.2, R_U7_3.2, R_U7_5.2, U7.11 (GND), U7.12 (GND), U7.17 (PAD); also elsewhere on the board
unnamed: D2.1 (C1), R_D2_1.2
unnamed: D2.2 (C2), R_D2_2.2
unnamed: Q3.3 (D), R_D2_2.1
unnamed: Q3.1 (G), R_D2_3.2
unnamed: C_U7_7.2, U7.15 (BTST)
unnamed: R_U7_2.1, U7.4 (ICHG)
unnamed: C_U7_9.1, U7.16 (PMID)
unnamed: R_U7_3.1, U7.9 (VSET)
V_REGN: C_U7_6.1, D2.4 (A), R_U7_4.1, U7.2 (REGN)

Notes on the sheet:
BQ25303J Datasheet
DESIGN NOTE: Charger with Power Path Management
[${#}] ${TITLE}
BQ25303
LED CHARGE INDICATOR

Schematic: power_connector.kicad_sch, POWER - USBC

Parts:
C_J1_1, C_J1_2: 3.3u; R_0603_1608Metric_Pad0.98x0.95mm_HandSolder
D_J1_1: GREEN; LED_0603_1608Metric; LCSC C2286
J1: TYPE-C-31-M-12; USB-C_SMD-TYPE-C-31-M-12; LCSC Part C165948
R_J1_D1_1: 2.2k; R_0402_1005Metric; LCSC C25091
U6: SMF05CT1G; SOT65P210X110-6N; LCSC C15879; not fitted

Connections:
/Project Architecture/POWER - CONNECTOR/CC1: J1.B5 (CC2); also elsewhere on the board
/Project Architecture/POWER - CONNECTOR/CC2: J1.A5 (CC1); also elsewhere on the board
/Project Architecture/POWER - POWER DELIVERY/V_USB_IN: C_J1_1.1, C_J1_2.1, D_J1_1.2 (A), J1.A4 (VBUS), J1.A9 (VBUS), J1.B4 (VBUS), J1.B9 (VBUS); also elsewhere on the board
GND: C_J1_1.2, C_J1_2.2, J1.0 (SHIELD), J1.1 (SHIELD), J1.2 (SHIELD), J1.3 (SHIELD), J1.A1 (GND), J1.A12 (GND), J1.B1 (GND), J1.B12 (GND), R_J1_D1_1.1, U6.2; also elsewhere on the board
unnamed: D_J1_1.1 (K), R_J1_D1_1.2

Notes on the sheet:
ESD
[${#}] ${TITLE}
USB
USB-C
